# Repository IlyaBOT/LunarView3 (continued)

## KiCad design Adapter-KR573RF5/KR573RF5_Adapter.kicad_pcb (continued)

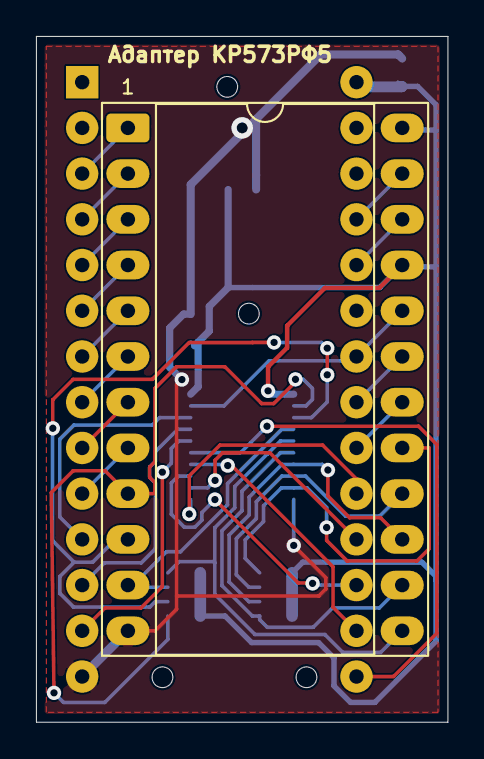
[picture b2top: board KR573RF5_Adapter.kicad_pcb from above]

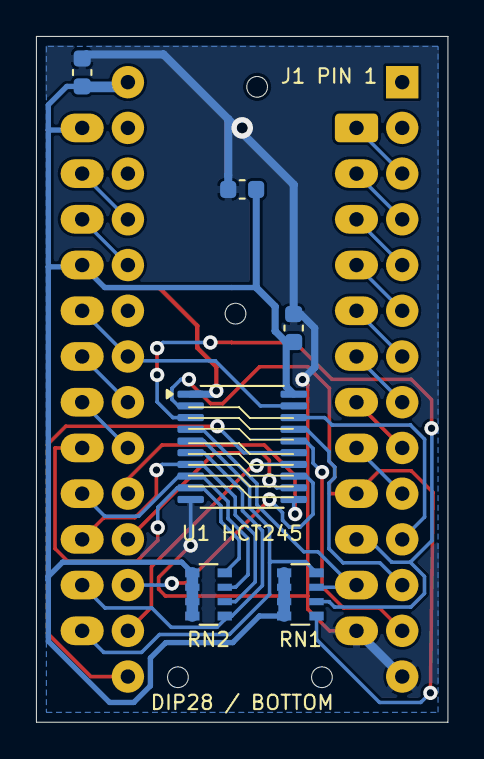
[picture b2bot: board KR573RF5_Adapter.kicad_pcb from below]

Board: 2 copper layers, 22.9 x 38.1 mm, 8 parts (7 on the bottom side), 31 nets.

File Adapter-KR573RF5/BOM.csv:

Reference,Value,Footprint,Side
J1,DIP28 male / bottom,ProjectFootprints:DIP28_Male_RoundPins_Bottom,bottom
J2,KR573RF5 socket DIP24,Package_DIP:DIP-24_W15.24mm_Socket_LongPads,top
U1,SN74HCT245PW,Package_SO:TSSOP-20_4.4x6.5mm_P0.65mm,bottom
C1,100nF / 16V,Capacitor_SMD:C_0603_1608Metric,bottom
C2,100nF / 16V,Capacitor_SMD:C_0603_1608Metric,bottom
C3,1uF / 10V,Capacitor_SMD:C_0603_1608Metric,bottom
RN1,4x47k CAY16-473J4LF,Resistor_SMD:R_Array_Convex_4x0603,bottom
RN2,4x47k CAY16-473J4LF,Resistor_SMD:R_Array_Convex_4x0603,bottom

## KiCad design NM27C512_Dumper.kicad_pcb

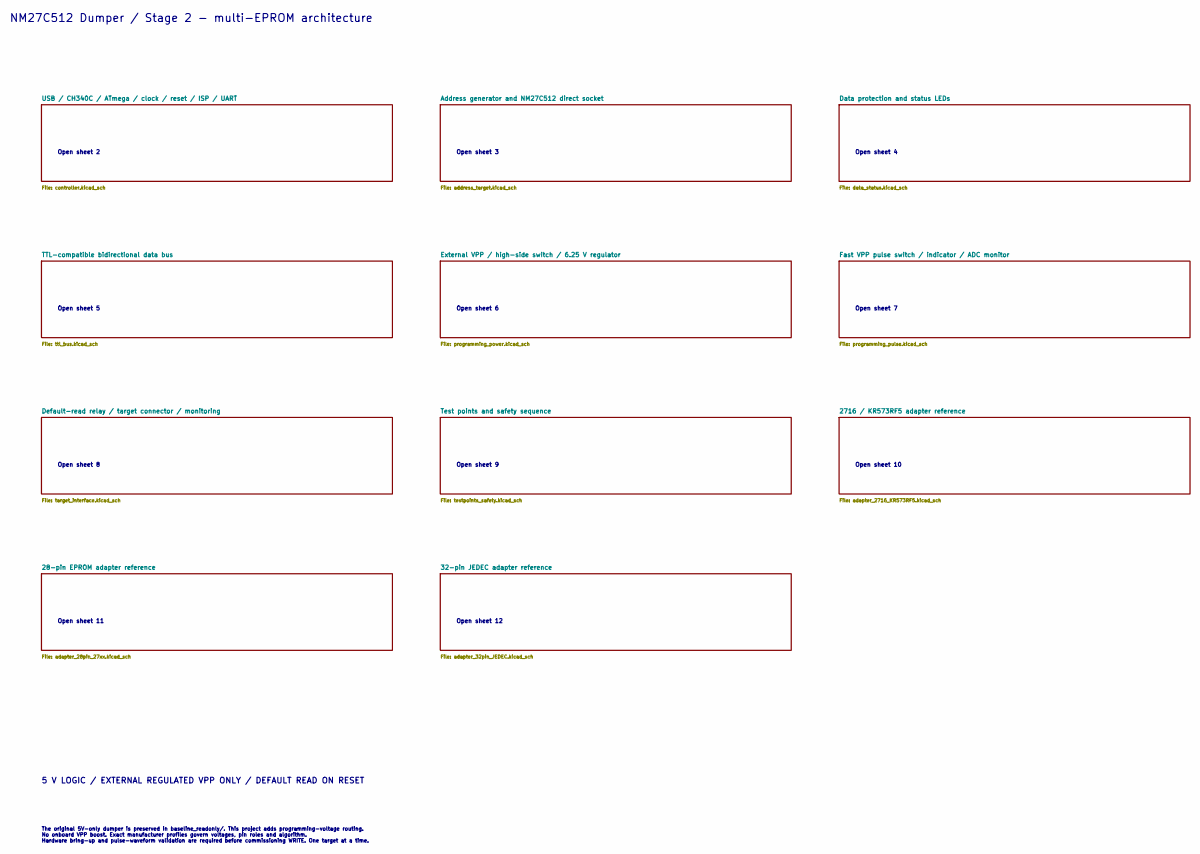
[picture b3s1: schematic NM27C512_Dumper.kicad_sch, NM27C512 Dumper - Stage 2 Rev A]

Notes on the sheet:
Open sheet 8
Open sheet 5
5 V LOGIC / EXTERNAL REGULATED VPP ONLY / DEFAULT READ ON RESET
Open sheet 12
Open sheet 9
Open sheet 7
Open sheet 3
Open sheet 4
Open sheet 2
Open sheet 10
Open sheet 11
The original 5V-only dumper is preserved in baseline_readonly/. This project adds programming-voltage routing. No onboard VPP boost. Exact manufacturer profiles govern voltages, pin roles and algorithm. Hardware bring-up and pulse-waveform validation are required before commissioning WRITE. One tar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
NM27C512 Dumper / Stage 2 - multi-EPROM architecture
Open sheet 6

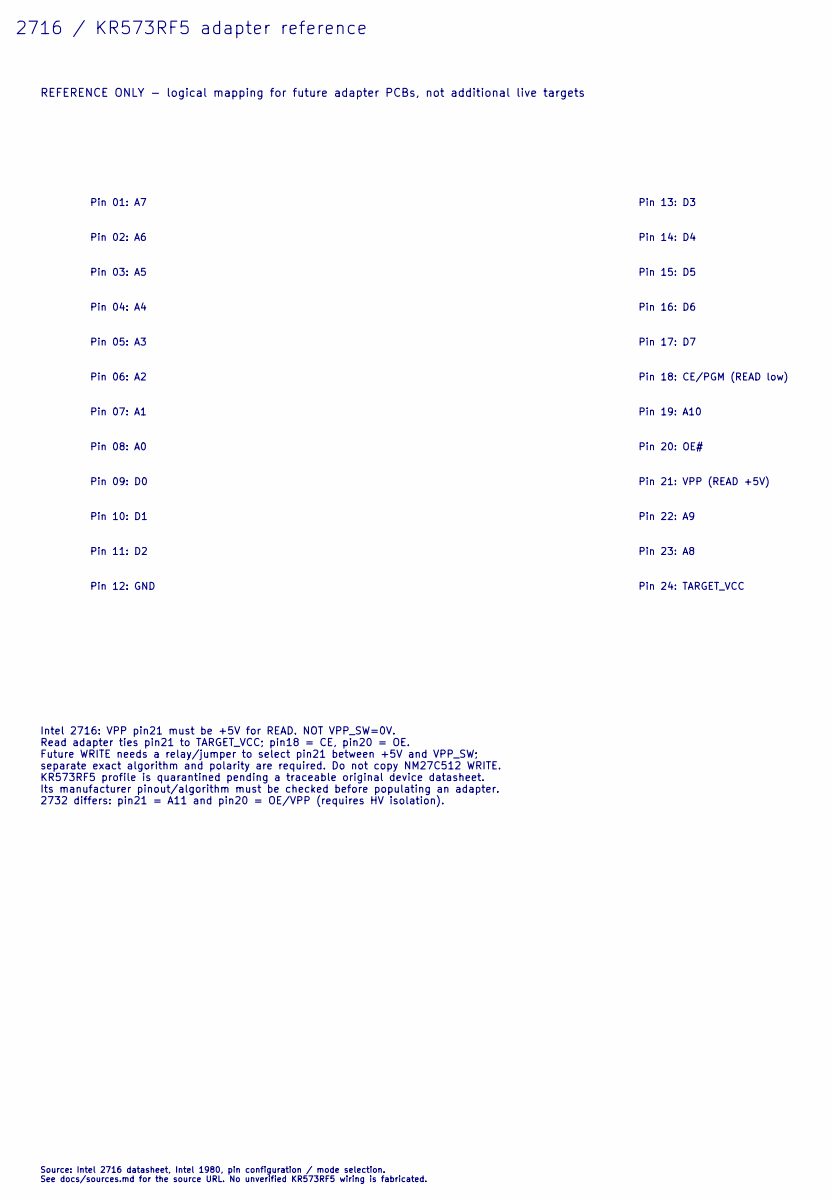
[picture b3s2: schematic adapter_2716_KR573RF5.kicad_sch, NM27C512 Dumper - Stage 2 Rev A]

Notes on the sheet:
Pin 16: D6
Pin 01: A7
Pin 06: A2
Pin 20: OE#
Pin 07: A1
Pin 21: VPP (READ +5V)
Pin 10: D1
Pin 14: D4
Pin 19: A10
Source: Intel 2716 datasheet, Intel 1980, pin configuration / mode selection. See docs/sources.md for the source URL. No unverified KR573RF5 wiring is fabricated.
Pin 08: A0
Pin 22: A9
Pin 24: TARGET_VCC
Pin 23: A8
Pin 13: D3
Pin 11: D2
Pin 15: D5
Pin 04: A4
Pin 03: A5
Pin 05: A3
Pin 17: D7
Pin 12: GND
REFERENCE ONLY - logical mapping for future adapter PCBs, not additional live targets
Intel 2716: VPP pin21 must be +5V for READ. NOT VPP_SW=0V. Read adapter ties pin21 to TARGET_VCC; pin18 = CE, pin20 = OE. Future WRITE needs a relay/jumper to select pin21 between +5V and VPP_SW; separate exact algorithm and polarity are required. Do not copy NM27C512 WRITE. KR573RF5 profile is qua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
Pin 09: D0
2716 / KR573RF5 adapter reference
Pin 18: CE/PGM (READ low)
Pin 02: A6

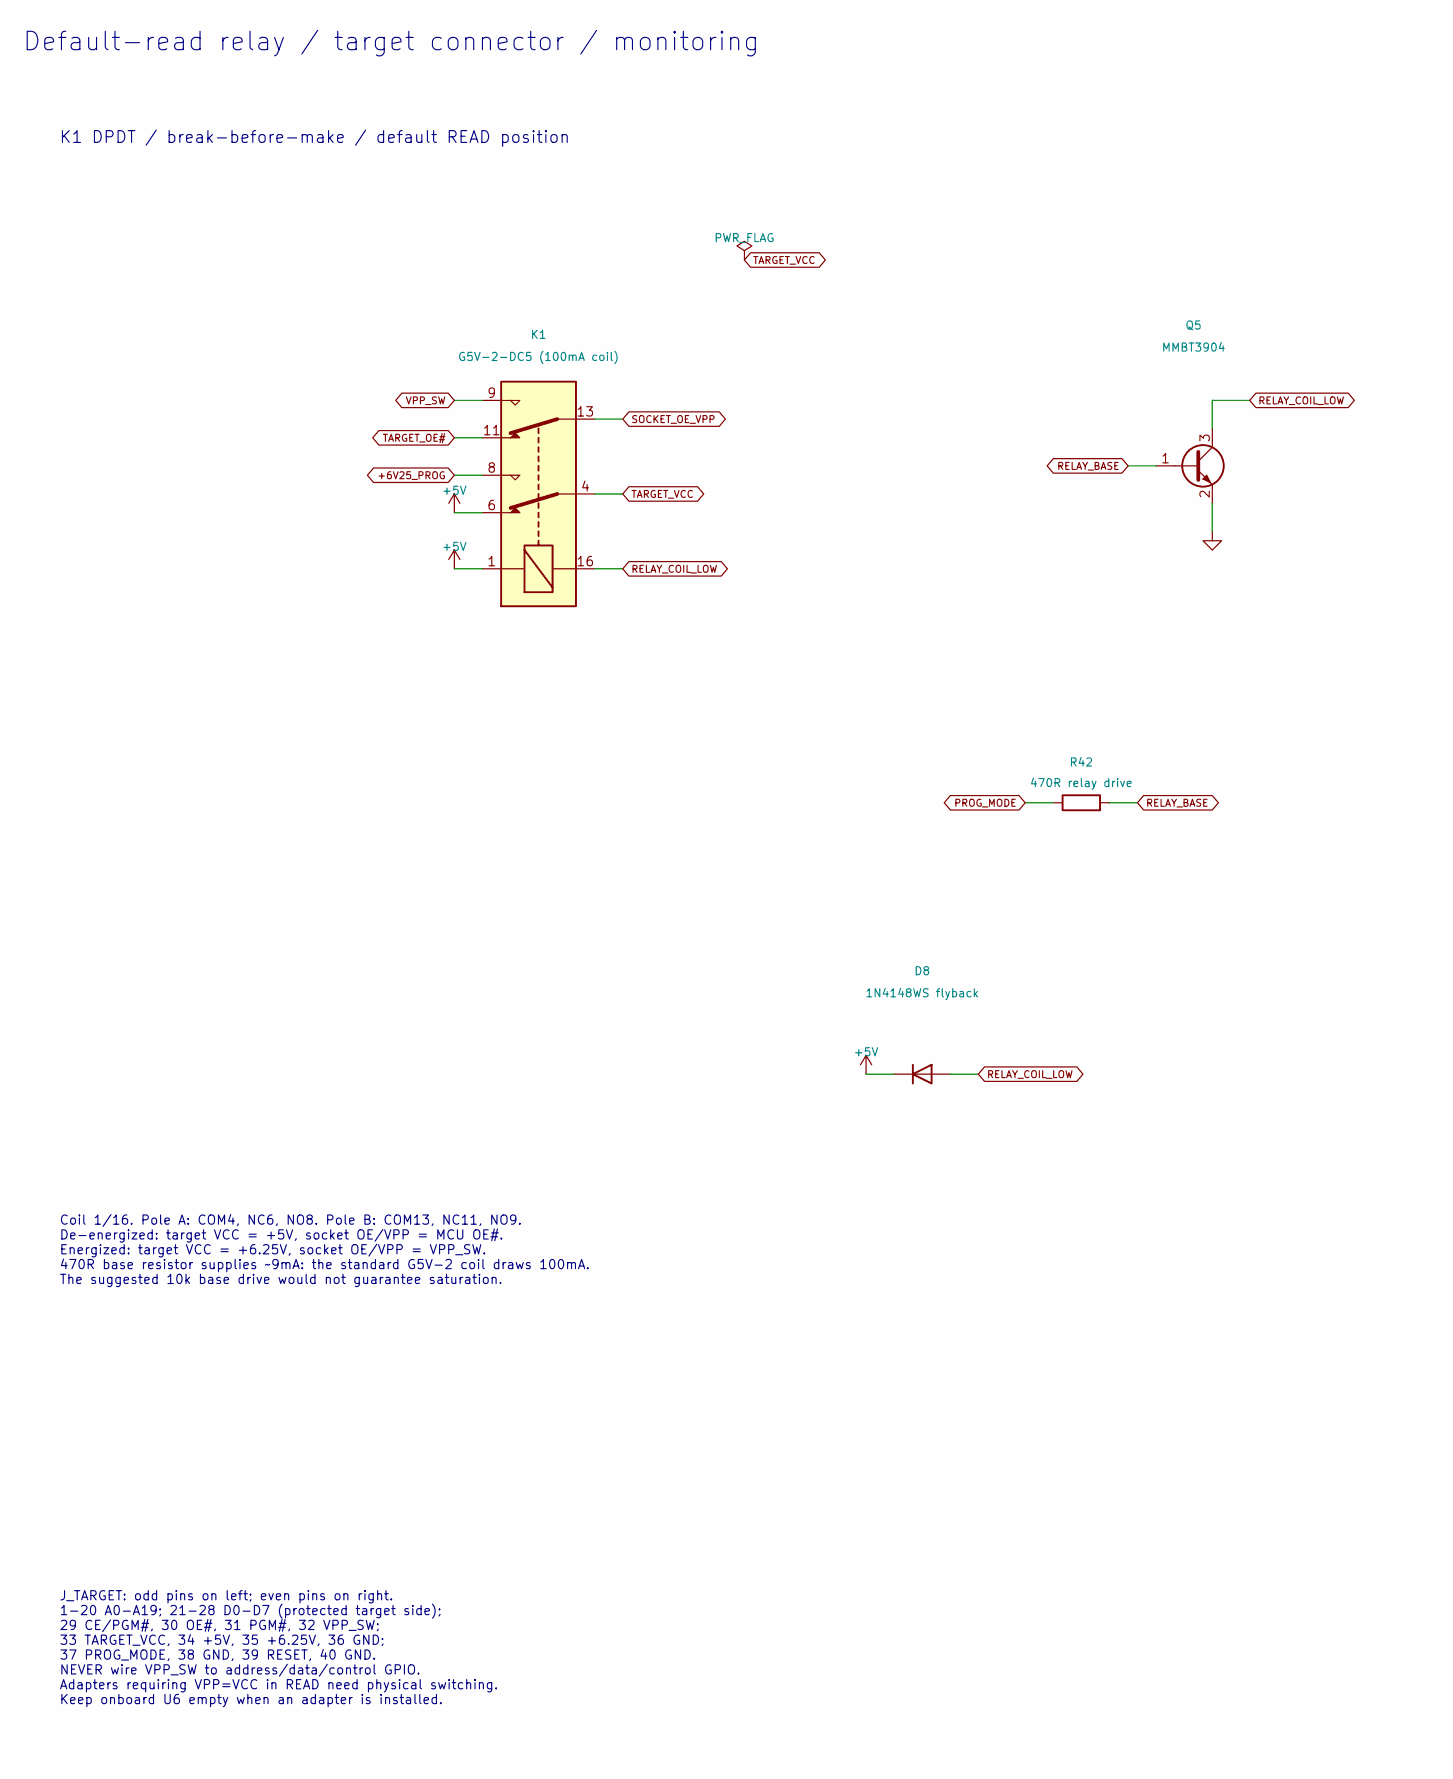
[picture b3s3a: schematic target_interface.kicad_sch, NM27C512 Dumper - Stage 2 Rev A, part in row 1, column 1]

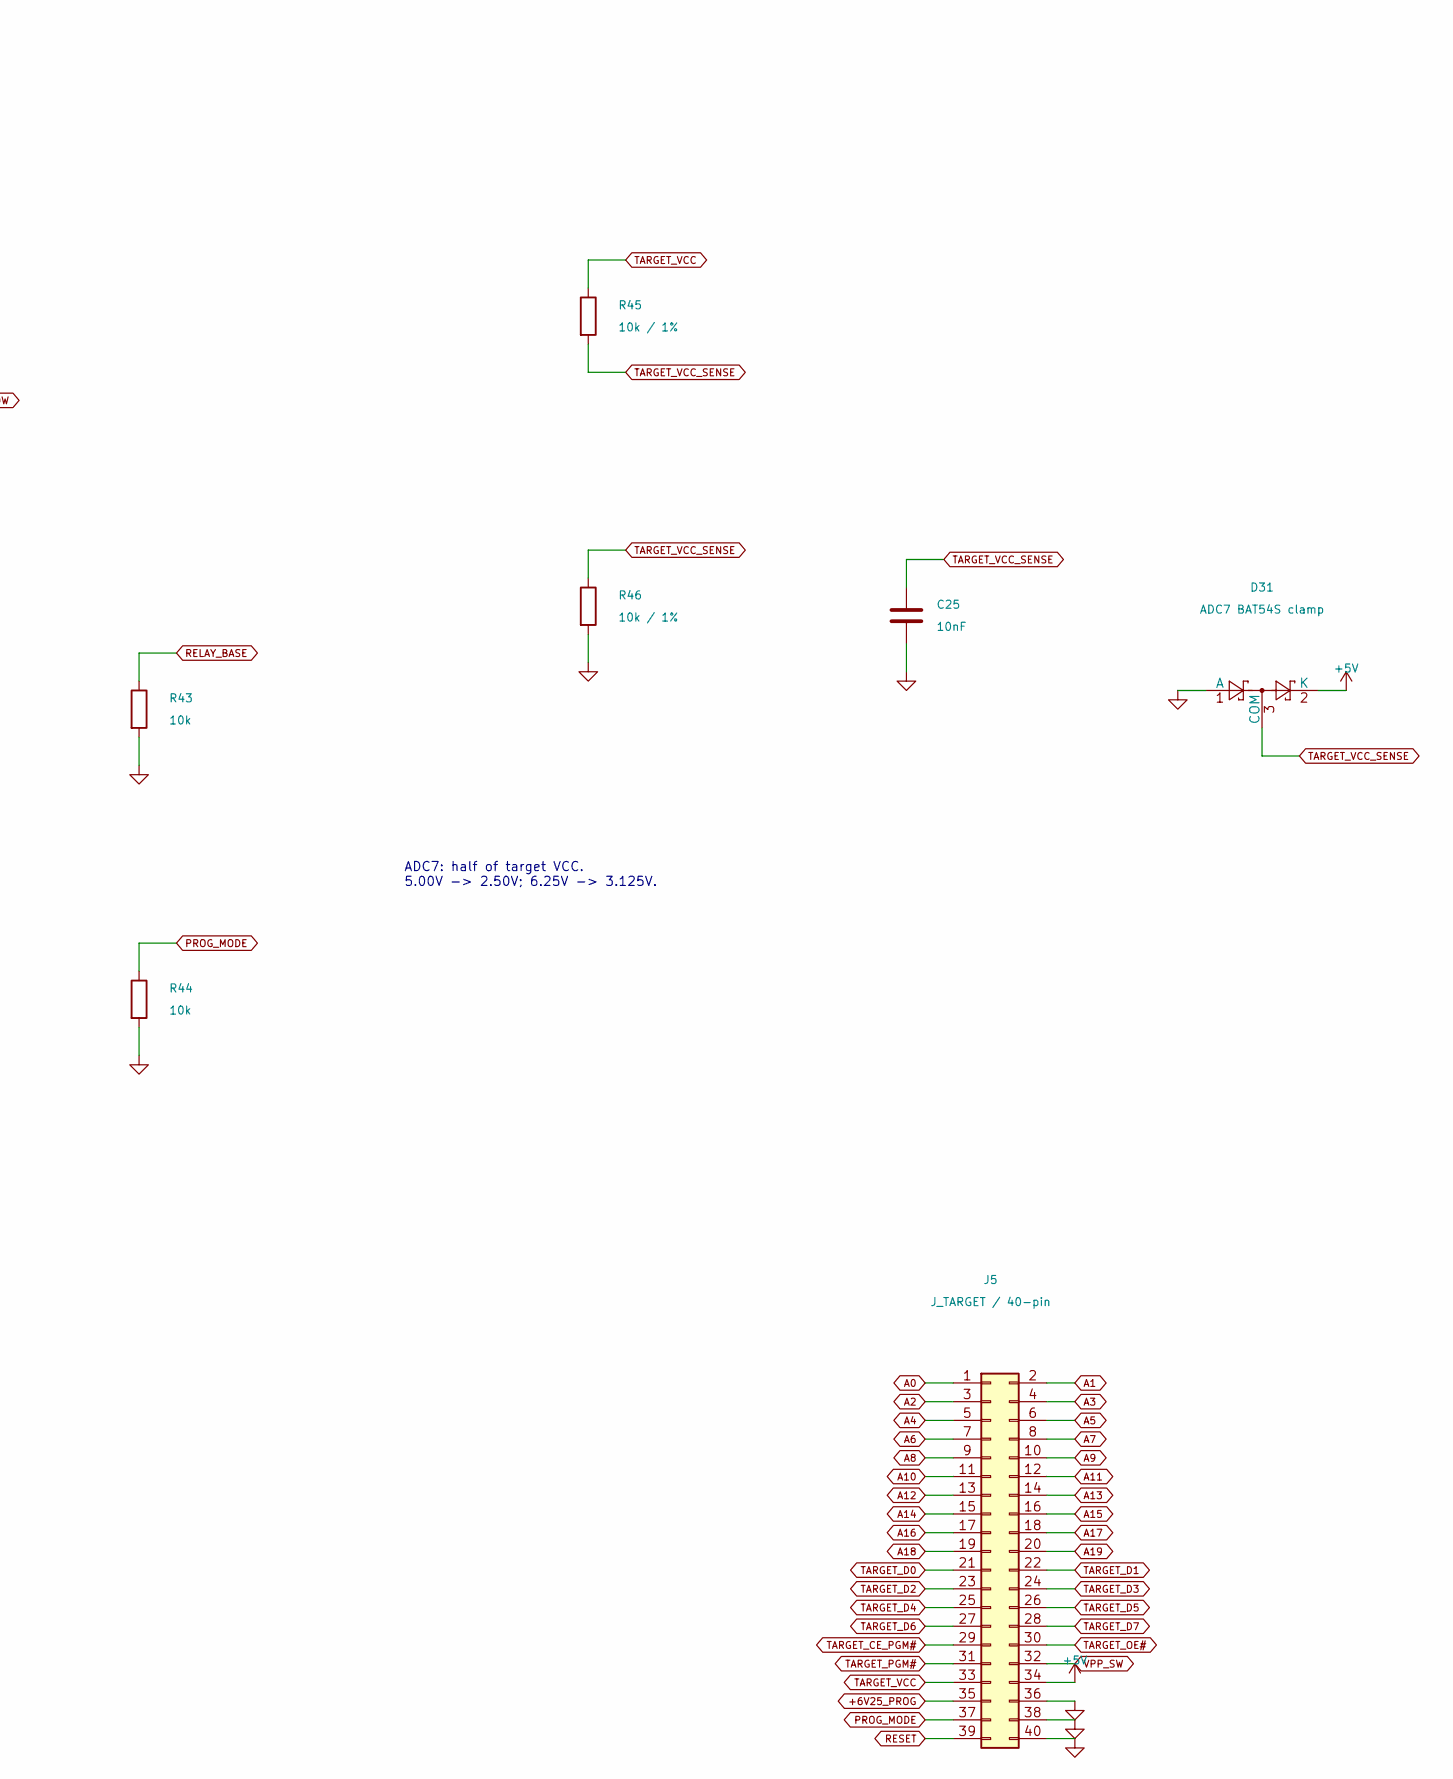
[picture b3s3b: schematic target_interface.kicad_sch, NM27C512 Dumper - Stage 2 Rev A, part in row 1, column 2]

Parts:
C25: 10nF; C_0603_1608Metric
D8: 1N4148WS flyback; D_SOD-323
D31: ADC7 BAT54S clamp; SOT-23
J5: J_TARGET / 40-pin; PinHeader_2x20_P2.54mm_Vertical
K1: G5V-2-DC5 (100mA coil); Relay_DPDT_Omron_G5V-2
Q5: MMBT3904; SOT-23
R42: 470R relay drive; R_0603_1608Metric
R43, R44: 10k; R_0603_1608Metric
R45, R46: 10k / 1%; R_0603_1608Metric

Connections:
+5V: D8.1 (K), D31.2 (K), J5.34, K1.1, K1.6; also elsewhere on the board
+6V25_PROG: J5.35, K1.8; also elsewhere on the board
A0: J5.1; also elsewhere on the board
A1: J5.2; also elsewhere on the board
A2: J5.3; also elsewhere on the board
A3: J5.4; also elsewhere on the board
A4: J5.5; also elsewhere on the board
A5: J5.6; also elsewhere on the board
A6: J5.7; also elsewhere on the board
A7: J5.8; also elsewhere on the board
A8: J5.9; also elsewhere on the board
A9: J5.10; also elsewhere on the board
A10: J5.11; also elsewhere on the board
A11: J5.12; also elsewhere on the board
A12: J5.13; also elsewhere on the board
A13: J5.14; also elsewhere on the board
A14: J5.15; also elsewhere on the board
A15: J5.16; also elsewhere on the board
A16: J5.17; also elsewhere on the board
A17: J5.18; also elsewhere on the board
A18: J5.19; also elsewhere on the board
A19: J5.20; also elsewhere on the board
GND: C25.2, D31.1 (A), J5.36, J5.38, J5.40, Q5.2 (E), R43.2, R44.2, R46.2; also elsewhere on the board
PROG_MODE: J5.37, R42.1, R44.1; also elsewhere on the board
RELAY_BASE: Q5.1 (B), R42.2, R43.1
RELAY_COIL_LOW: D8.2 (A), K1.16, Q5.3 (C)
RESET: J5.39; also elsewhere on the board
SOCKET_OE_VPP: K1.13; also elsewhere on the board
TARGET_CE_PGM#: J5.29; also elsewhere on the board
TARGET_D0: J5.21; also elsewhere on the board
TARGET_D1: J5.22; also elsewhere on the board
TARGET_D2: J5.23; also elsewhere on the board
TARGET_D3: J5.24; also elsewhere on the board
TARGET_D4: J5.25; also elsewhere on the board
TARGET_D5: J5.26; also elsewhere on the board
TARGET_D6: J5.27; also elsewhere on the board
TARGET_D7: J5.28; also elsewhere on the board
TARGET_OE#: J5.30, K1.11; also elsewhere on the board
TARGET_PGM#: J5.31; also elsewhere on the board
TARGET_VCC: J5.33, K1.4, R45.1; also elsewhere on the board
TARGET_VCC_SENSE: C25.1, D31.3 (COM), R45.2, R46.1; also elsewhere on the board
VPP_SW: J5.32, K1.9; also elsewhere on the board

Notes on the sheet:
Coil 1/16. Pole A: COM4, NC6, NO8. Pole B: COM13, NC11, NO9. De-energized: target VCC = +5V, socket OE/VPP = MCU OE#. Energized: target VCC = +6.25V, socket OE/VPP = VPP_SW. 470R base resistor supplies ~9mA: the standard G5V-2 coil draws 100mA. The suggested 10k base drive would not guarantee satur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
K1 DPDT / break-before-make / default READ position
Default-read relay / target connector / monitoring
J_TARGET: odd pins on left; even pins on right. 1-20 A0-A19; 21-28 D0-D7 (protected target side); 29 CE/PGM#, 30 OE#, 31 PGM#, 32 VPP_SW; 33 TARGET_VCC, 34 +5V, 35 +6.25V, 36 GND; 37 PROG_MODE, 38 GND, 39 RESET, 40 GND. NEVER wire VPP_SW to address/data/control GPIO. Adapters requiring VPP=VCC in R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
ADC7: half of target VCC. 5.00V -> 2.50V; 6.25V -> 3.125V.

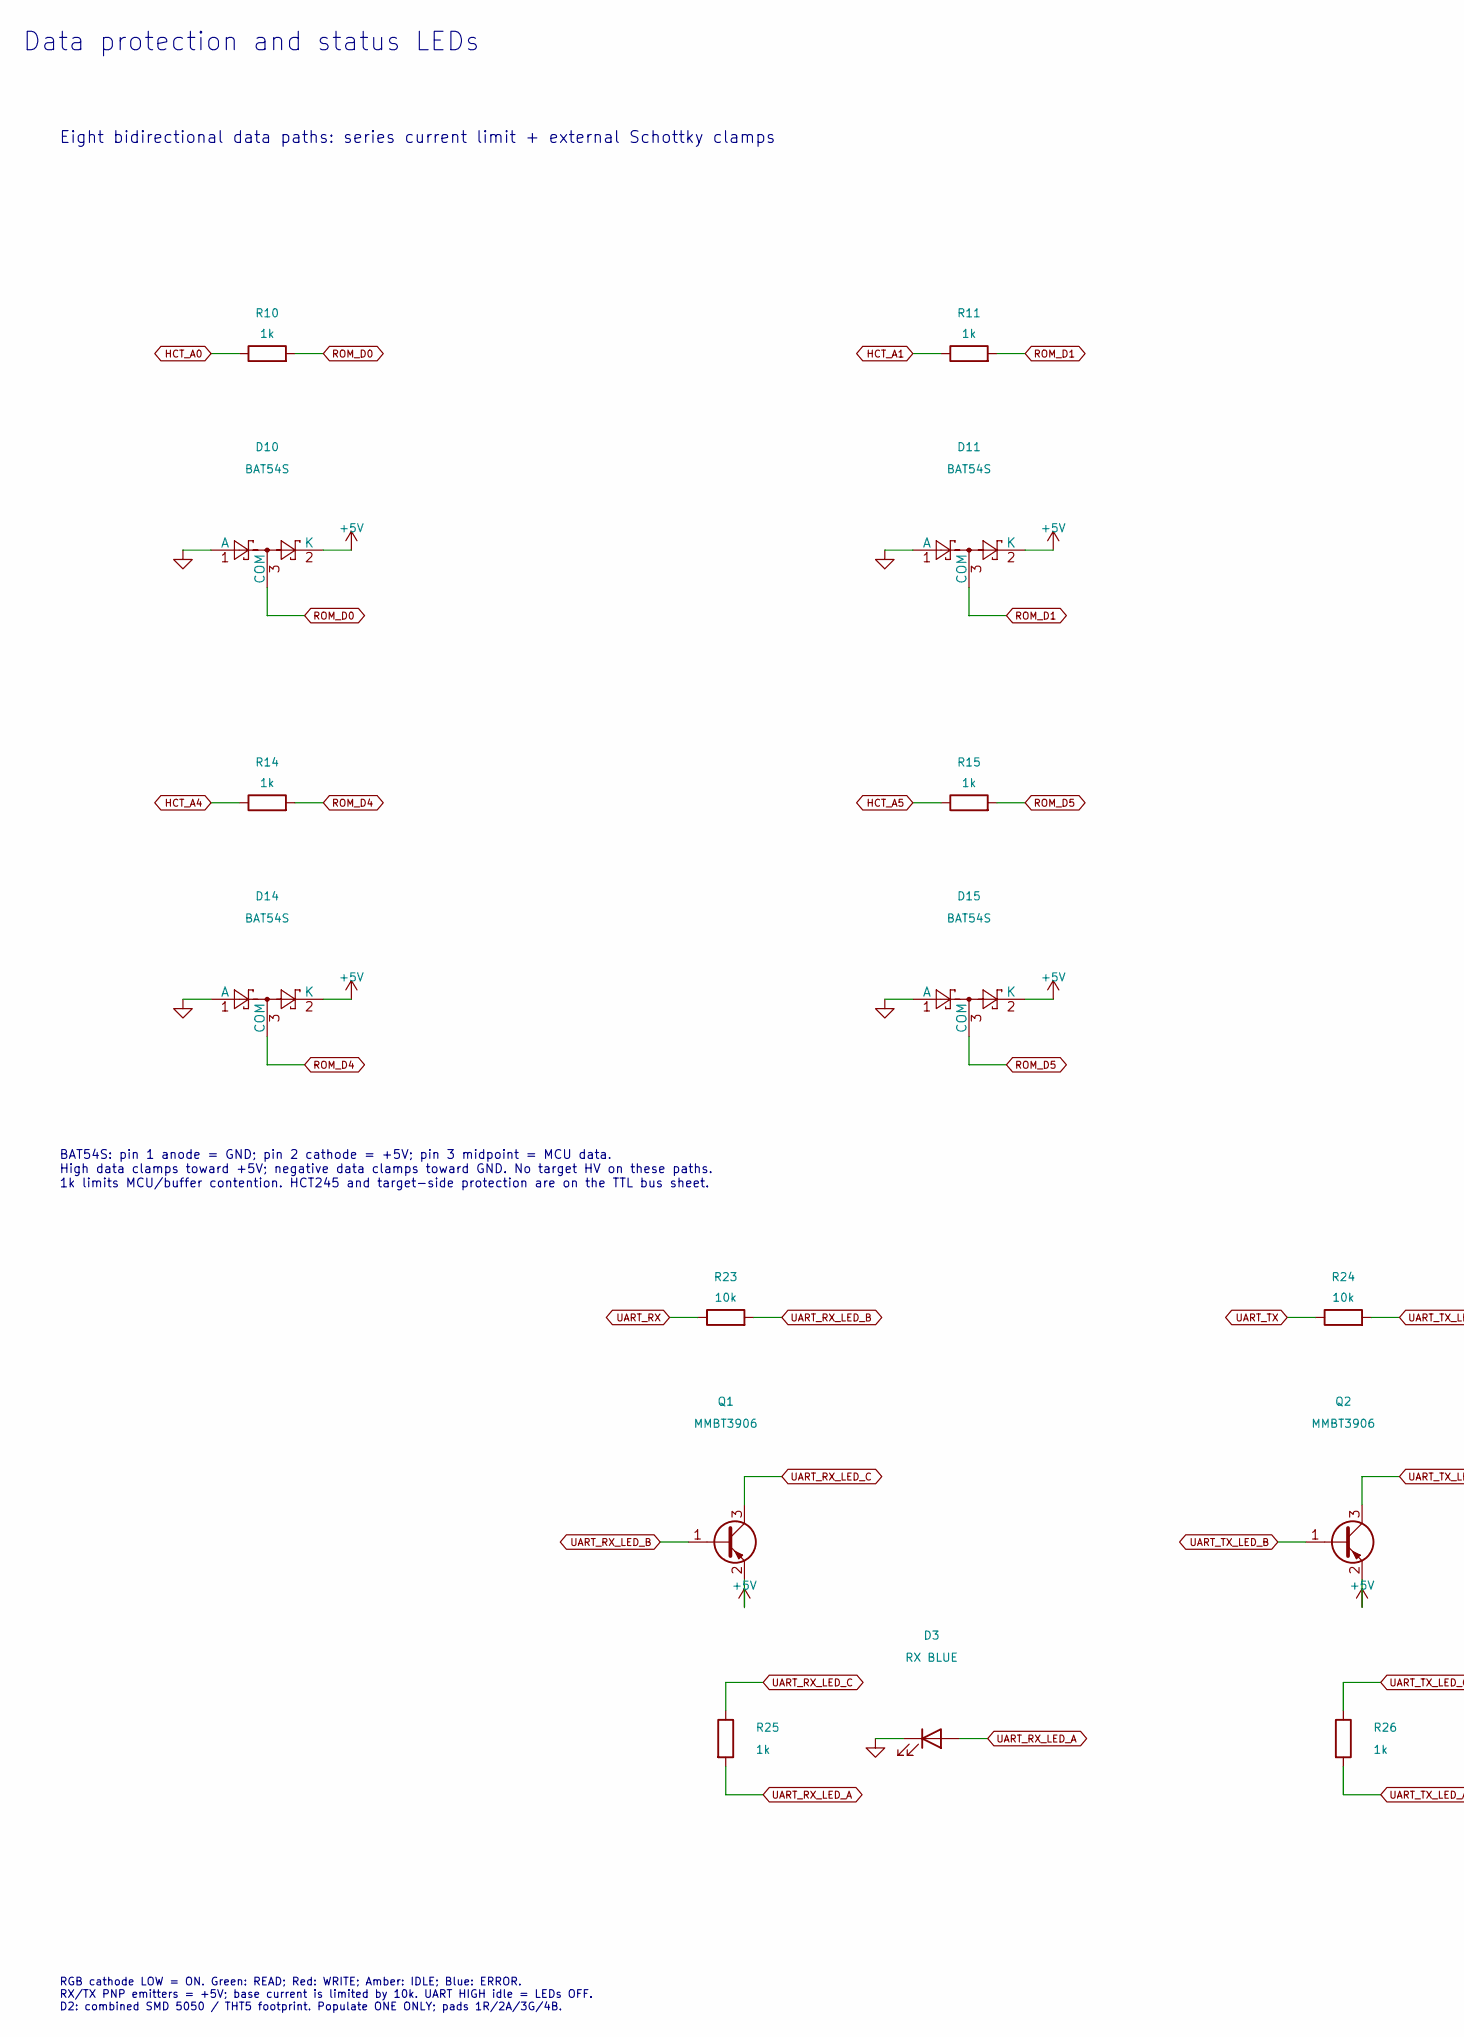
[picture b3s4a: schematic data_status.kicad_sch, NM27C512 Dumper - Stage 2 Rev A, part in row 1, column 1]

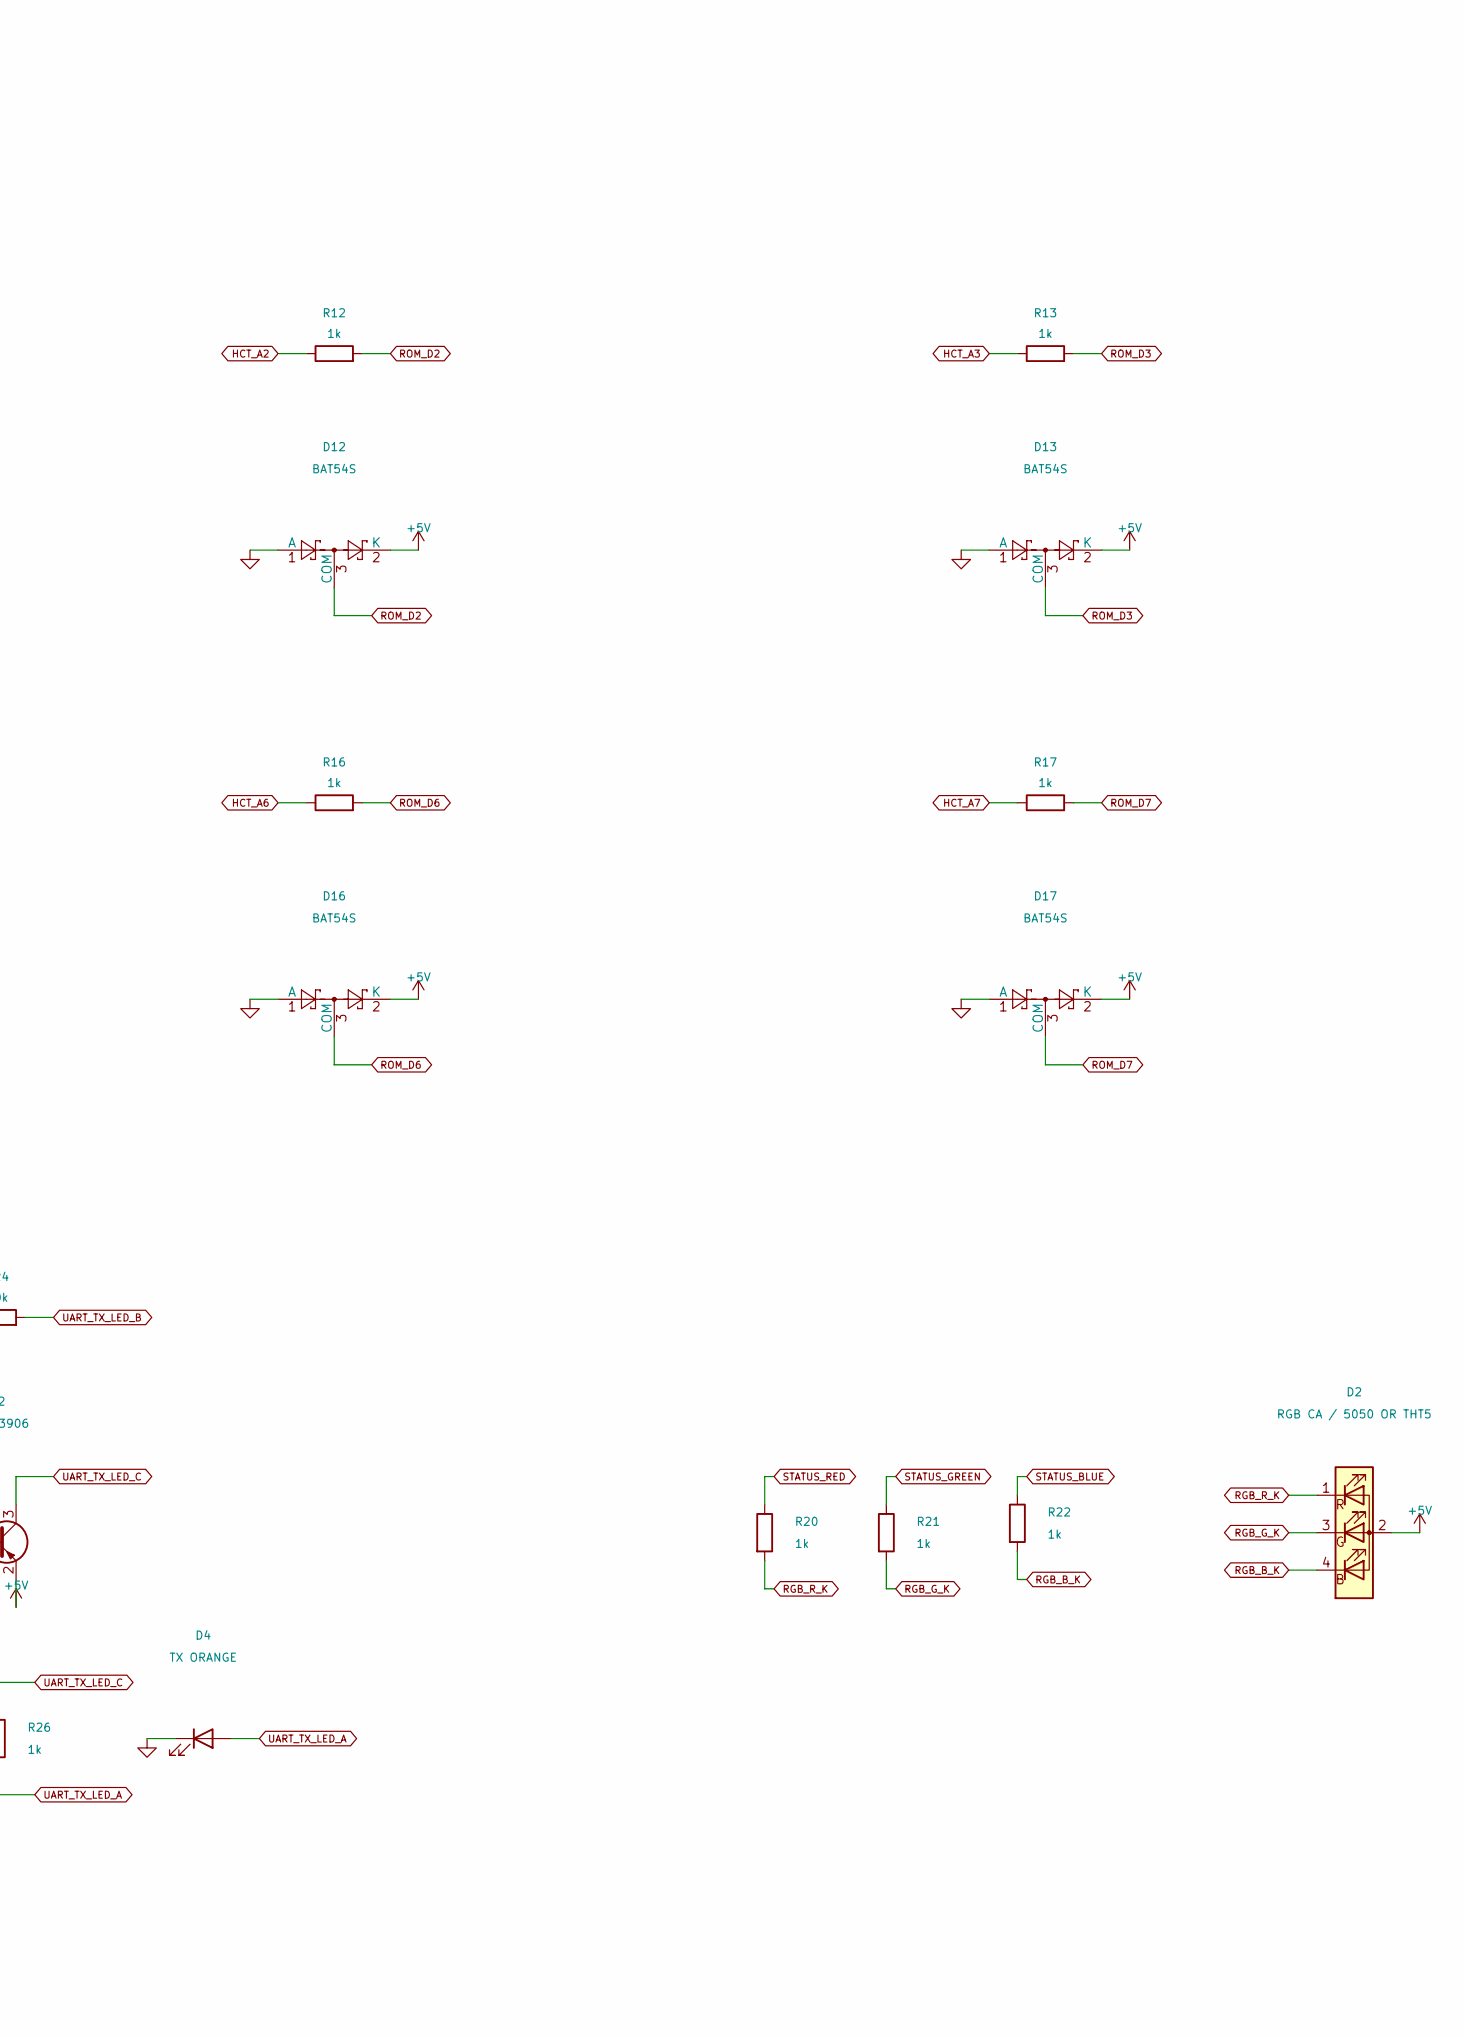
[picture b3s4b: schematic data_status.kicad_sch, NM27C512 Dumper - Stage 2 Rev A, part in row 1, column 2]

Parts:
D2: RGB CA / 5050 OR THT5; RGB_CA_5050_or_THT5
D3: RX BLUE; LED_0603_1608Metric
D4: TX ORANGE; LED_0603_1608Metric
D10, D11, D12, D13, D14, D15, D16, D17: BAT54S; SOT-23
Q1, Q2: MMBT3906; SOT-23
R10, R11, R12, R13, R14, R15, R16, R17, R20, R21, R22, R25, R26: 1k; R_0603_1608Metric
R23, R24: 10k; R_0603_1608Metric

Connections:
+5V: D2.2 (A), D10.2 (K), D11.2 (K), D12.2 (K), D13.2 (K), D14.2 (K), D15.2 (K), D16.2 (K), D17.2 (K), Q1.2 (E), Q2.2 (E); also elsewhere on the board
GND: D3.1 (K), D4.1 (K), D10.1 (A), D11.1 (A), D12.1 (A), D13.1 (A), D14.1 (A), D15.1 (A), D16.1 (A), D17.1 (A); also elsewhere on the board
HCT_A0: R10.1; also elsewhere on the board
HCT_A1: R11.1; also elsewhere on the board
HCT_A2: R12.1; also elsewhere on the board
HCT_A3: R13.1; also elsewhere on the board
HCT_A4: R14.1; also elsewhere on the board
HCT_A5: R15.1; also elsewhere on the board
HCT_A6: R16.1; also elsewhere on the board
HCT_A7: R17.1; also elsewhere on the board
RGB_B_K: D2.4 (B), R22.2
RGB_G_K: D2.3 (G), R21.2
RGB_R_K: D2.1 (R), R20.2
ROM_D0: D10.3 (COM), R10.2; also elsewhere on the board
ROM_D1: D11.3 (COM), R11.2; also elsewhere on the board
ROM_D2: D12.3 (COM), R12.2; also elsewhere on the board
ROM_D3: D13.3 (COM), R13.2; also elsewhere on the board
ROM_D4: D14.3 (COM), R14.2; also elsewhere on the board
ROM_D5: D15.3 (COM), R15.2; also elsewhere on the board
ROM_D6: D16.3 (COM), R16.2; also elsewhere on the board
ROM_D7: D17.3 (COM), R17.2; also elsewhere on the board
STATUS_BLUE: R22.1; also elsewhere on the board
STATUS_GREEN: R21.1; also elsewhere on the board
STATUS_RED: R20.1; also elsewhere on the board
UART_RX: R23.1; also elsewhere on the board
UART_RX_LED_A: D3.2 (A), R25.2
UART_RX_LED_B: Q1.1 (B), R23.2
UART_RX_LED_C: Q1.3 (C), R25.1
UART_TX: R24.1; also elsewhere on the board
UART_TX_LED_A: D4.2 (A), R26.2
UART_TX_LED_B: Q2.1 (B), R24.2
UART_TX_LED_C: Q2.3 (C), R26.1

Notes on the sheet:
BAT54S: pin 1 anode = GND; pin 2 cathode = +5V; pin 3 midpoint = MCU data. High data clamps toward +5V; negative data clamps toward GND. No target HV on these paths. 1k limits MCU/buffer contention. HCT245 and target-side protection are on the TTL bus sheet.
Data protection and status LEDs
RGB cathode LOW = ON. Green: READ; Red: WRITE; Amber: IDLE; Blue: ERROR. RX/TX PNP emitters = +5V; base current is limited by 10k. UART HIGH idle = LEDs OFF. D2: combined SMD 5050 / THT5 footprint. Populate ONE ONLY; pads 1R/2A/3G/4B.
Eight bidirectional data paths: series current limit + external Schottky clamps
